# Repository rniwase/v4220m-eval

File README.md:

# v4220m-eval
V4220M Audio Codec IC Evaluation Board

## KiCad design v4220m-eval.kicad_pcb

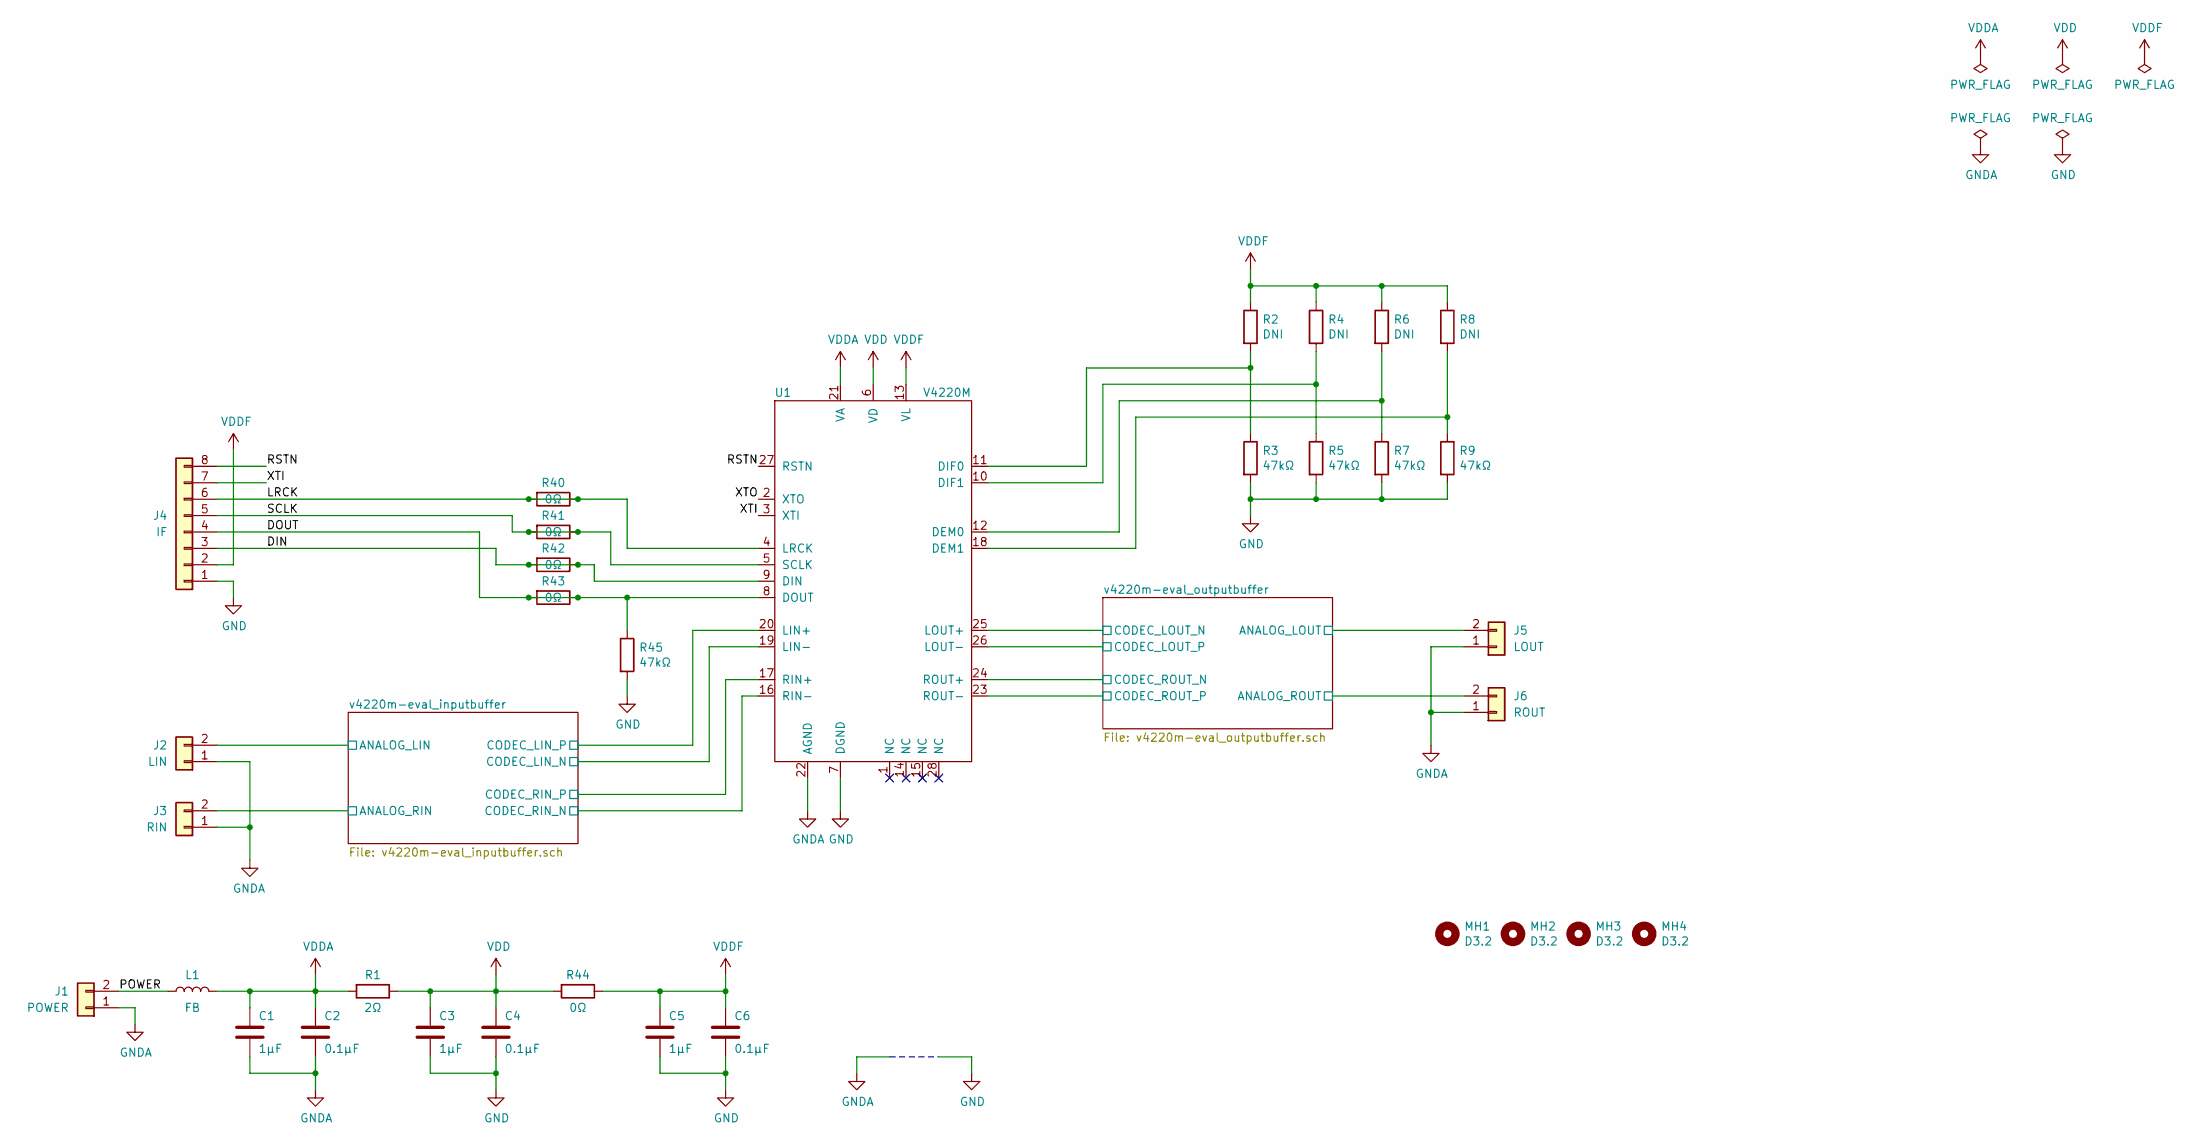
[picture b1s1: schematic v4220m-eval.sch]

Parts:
C1, C3, C5: 1μF; C_0603_1608Metric_Pad1.05x0.95mm_HandSolder
C2, C4, C6: 0.1μF; C_0603_1608Metric_Pad1.05x0.95mm_HandSolder
J1: POWER; PinHeader_1x02_P2.54mm_Vertical
J2: LIN; PinHeader_1x02_P2.54mm_Vertical
J3: RIN; PinHeader_1x02_P2.54mm_Vertical
J4: IF; PinHeader_1x08_P2.54mm_Vertical
J5: LOUT; PinHeader_1x02_P2.54mm_Vertical
J6: ROUT; PinHeader_1x02_P2.54mm_Vertical
L1: FB; L_0603_1608Metric_Pad1.05x0.95mm_HandSolder
MH1, MH2, MH3, MH4: D3.2; MountingHole_3.2mm_M3
R1: 2Ω; R_0603_1608Metric_Pad1.05x0.95mm_HandSolder
R2, R4, R6, R8: DNI; R_0603_1608Metric_Pad1.05x0.95mm_HandSolder
R3, R5, R7, R9, R45: 47kΩ; R_0603_1608Metric_Pad1.05x0.95mm_HandSolder
R40, R41, R42, R43, R44: 0Ω; R_0603_1608Metric_Pad1.05x0.95mm_HandSolder
U1: V4220M; SSOP-28_5.3x10.2mm_P0.65mm

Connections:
/DIN: J4.3, R42.1, R42.2, U1.9 (DIN)
/DOUT: J4.4, R43.1, R43.2, R45.1, U1.8 (DOUT)
/LRCK: J4.6, R40.1, R40.2, U1.4 (LRCK)
/POWER: J1.2, L1.1
/RSTN: J4.8, U1.27 (RSTN)
/SCLK: J4.5, R41.1, R41.2, U1.5 (SCLK)
/XTI: J4.7, U1.3 (XTI)
/v4220m-eval_inputbuffer/ANALOG_LIN: J2.2; also elsewhere on the board
/v4220m-eval_inputbuffer/ANALOG_RIN: J3.2; also elsewhere on the board
/v4220m-eval_inputbuffer/CODEC_LIN_N: U1.19 (LIN-); also elsewhere on the board
/v4220m-eval_inputbuffer/CODEC_LIN_P: U1.20 (LIN+); also elsewhere on the board
/v4220m-eval_inputbuffer/CODEC_RIN_N: U1.16 (RIN-); also elsewhere on the board
/v4220m-eval_inputbuffer/CODEC_RIN_P: U1.17 (RIN+); also elsewhere on the board
/v4220m-eval_outputbuffer/ANALOG_LOUT: J5.2; also elsewhere on the board
/v4220m-eval_outputbuffer/ANALOG_ROUT: J6.2; also elsewhere on the board
/v4220m-eval_outputbuffer/CODEC_LOUT_N: U1.25 (LOUT+); also elsewhere on the board
/v4220m-eval_outputbuffer/CODEC_LOUT_P: U1.26 (LOUT-); also elsewhere on the board
/v4220m-eval_outputbuffer/CODEC_ROUT_N: U1.24 (ROUT+); also elsewhere on the board
/v4220m-eval_outputbuffer/CODEC_ROUT_P: U1.23 (ROUT-); also elsewhere on the board
GND: C3.2, C4.2, C5.2, C6.2, J4.1, R3.2, R5.2, R7.2, R9.2, R45.2, U1.7 (DGND)
GNDA: C1.2, C2.2, J1.1, J2.1, J3.1, J5.1, J6.1, U1.22 (AGND); also elsewhere on the board
unnamed: R2.2, R3.1, U1.11 (DIF0)
unnamed: R4.2, R5.1, U1.10 (DIF1)
unnamed: R6.2, R7.1, U1.12 (DEM0)
unnamed: R8.2, R9.1, U1.18 (DEM1)
VDD: C3.1, C4.1, R1.1, R44.2, U1.6 (VD)
VDDA: C1.1, C2.1, L1.2, R1.2, U1.21 (VA); also elsewhere on the board
VDDF: C5.1, C6.1, J4.2, R2.1, R4.1, R6.1, R8.1, R44.1, U1.13 (VL)

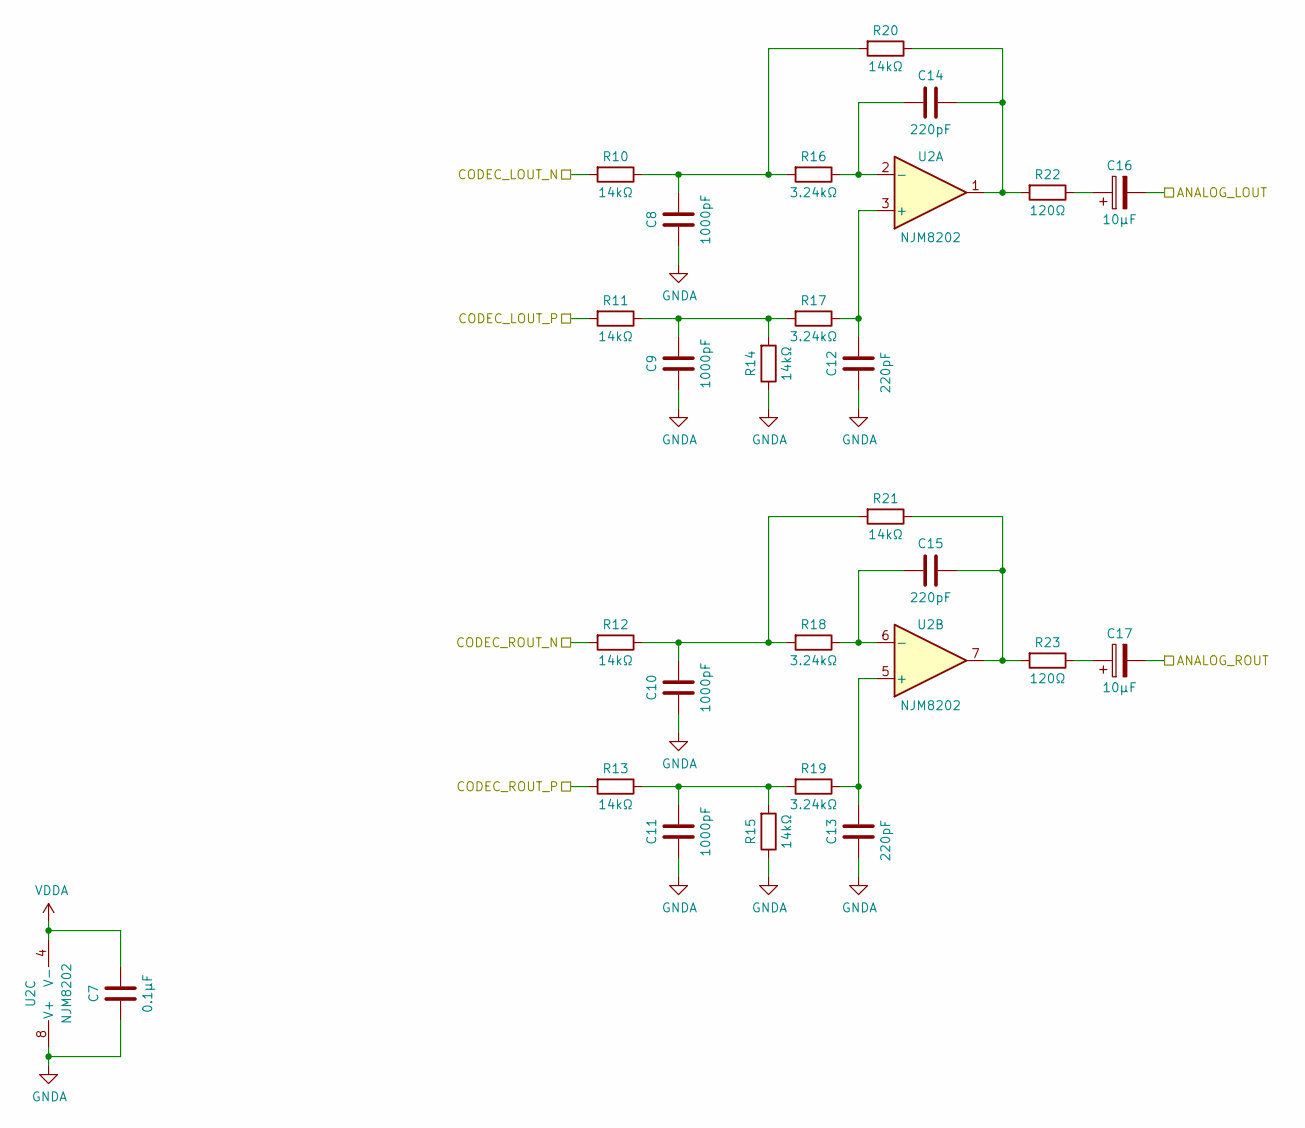
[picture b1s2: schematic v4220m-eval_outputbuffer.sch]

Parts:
C7: 0.1μF; C_0603_1608Metric_Pad1.05x0.95mm_HandSolder
C8, C9, C10, C11: 1000pF; C_0603_1608Metric_Pad1.05x0.95mm_HandSolder
C12, C13, C14, C15: 220pF; C_0603_1608Metric_Pad1.05x0.95mm_HandSolder
C16, C17: 10μF; CP_Elec_4x5.3
R10, R11, R12, R13, R14, R15, R20, R21: 14kΩ; R_0603_1608Metric_Pad1.05x0.95mm_HandSolder
R16, R17, R18, R19: 3.24kΩ; R_0603_1608Metric_Pad1.05x0.95mm_HandSolder
R22, R23: 120Ω; R_0603_1608Metric_Pad1.05x0.95mm_HandSolder
U2: NJM8202; MSOP-8_3x3mm_P0.65mm

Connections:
/v4220m-eval_outputbuffer/ANALOG_LOUT: C16.2; also elsewhere on the board
/v4220m-eval_outputbuffer/ANALOG_ROUT: C17.2; also elsewhere on the board
/v4220m-eval_outputbuffer/CODEC_LOUT_N: R10.2; also elsewhere on the board
/v4220m-eval_outputbuffer/CODEC_LOUT_P: R11.2; also elsewhere on the board
/v4220m-eval_outputbuffer/CODEC_ROUT_N: R12.2; also elsewhere on the board
/v4220m-eval_outputbuffer/CODEC_ROUT_P: R13.2; also elsewhere on the board
GNDA: C7.1, C8.1, C9.1, C10.1, C11.1, C12.1, C13.1, R14.1, R15.1, U2.8 (V+); also elsewhere on the board
unnamed: C8.2, R10.1, R16.2, R20.2
unnamed: C9.2, R11.1, R14.2, R17.2
unnamed: C10.2, R12.1, R18.2, R21.2
unnamed: C11.2, R13.1, R15.2, R19.2
unnamed: C12.2, R17.1, U2.3 (+)
unnamed: C13.2, R19.1, U2.5 (+)
unnamed: C14.1, R20.1, R22.2, U2.1
unnamed: C14.2, R16.1, U2.2 (-)
unnamed: C15.1, R21.1, R23.2, U2.7
unnamed: C15.2, R18.1, U2.6 (-)
unnamed: C16.1, R22.1
unnamed: C17.1, R23.1
VDDA: C7.2, U2.4 (V-); also elsewhere on the board

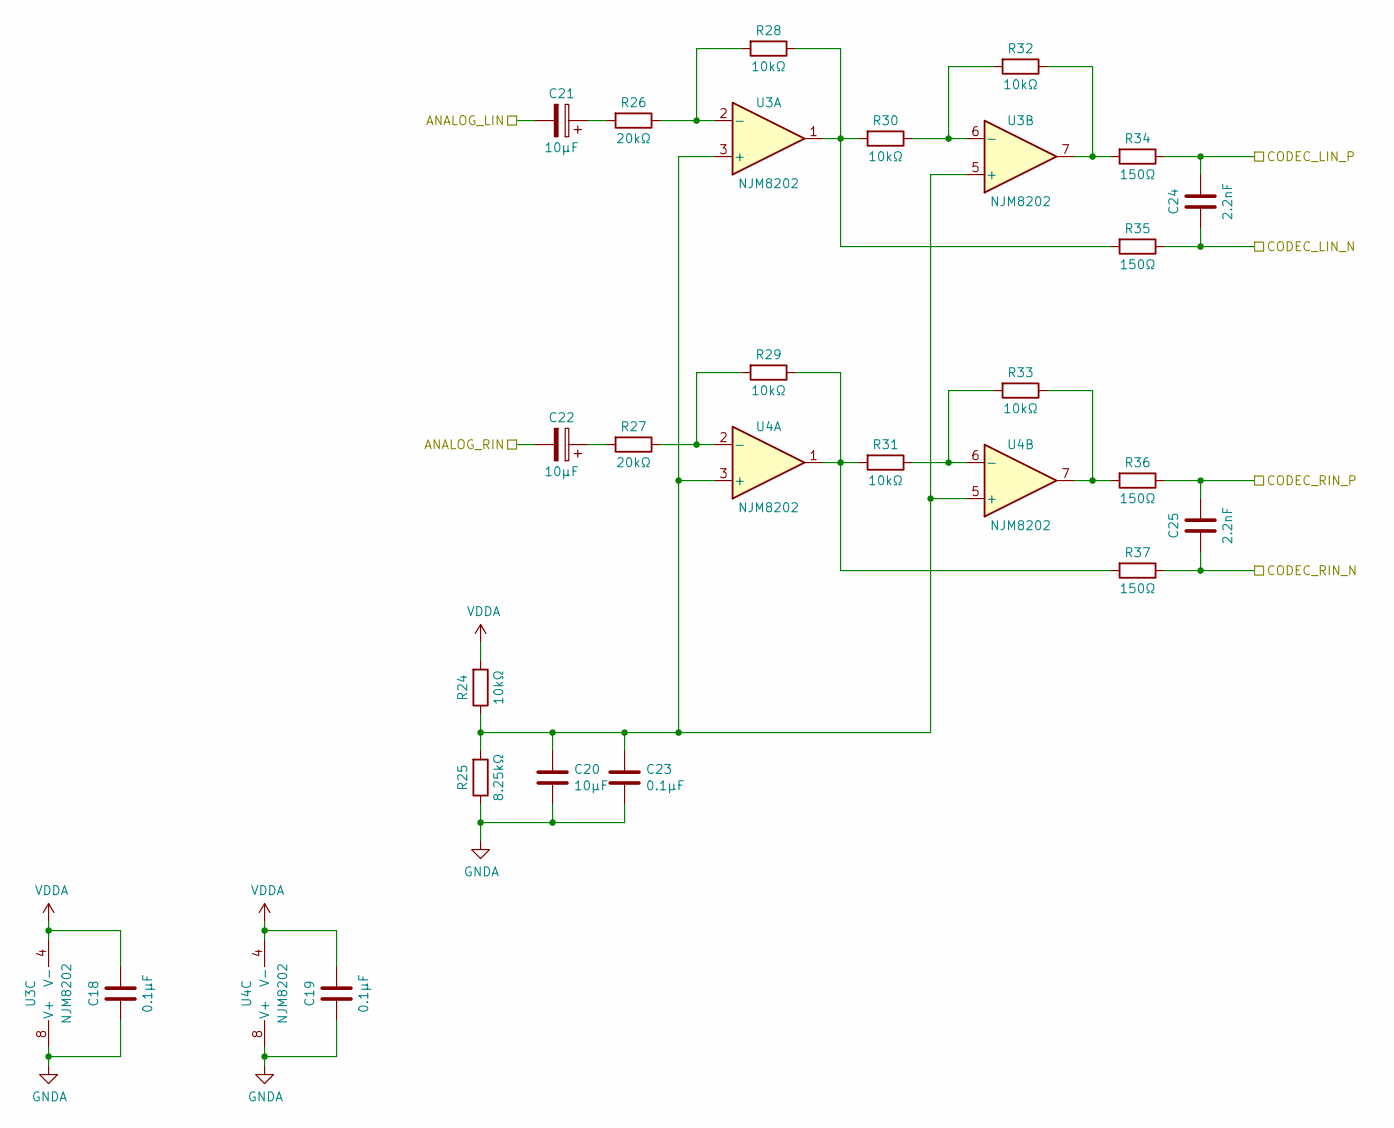
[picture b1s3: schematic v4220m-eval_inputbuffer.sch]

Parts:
C18, C19, C23: 0.1μF; C_0603_1608Metric_Pad1.05x0.95mm_HandSolder
C20: 10μF; C_0603_1608Metric_Pad1.05x0.95mm_HandSolder
C21, C22: 10μF; CP_Elec_4x5.3
C24, C25: 2.2nF; C_0603_1608Metric_Pad1.05x0.95mm_HandSolder
R24, R28, R29, R30, R31, R32, R33: 10kΩ; R_0603_1608Metric_Pad1.05x0.95mm_HandSolder
R25: 8.25kΩ; R_0603_1608Metric_Pad1.05x0.95mm_HandSolder
R26, R27: 20kΩ; R_0603_1608Metric_Pad1.05x0.95mm_HandSolder
R34, R35, R36, R37: 150Ω; R_0603_1608Metric_Pad1.05x0.95mm_HandSolder
U3, U4: NJM8202; MSOP-8_3x3mm_P0.65mm

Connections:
/v4220m-eval_inputbuffer/ANALOG_LIN: C21.2; also elsewhere on the board
/v4220m-eval_inputbuffer/ANALOG_RIN: C22.2; also elsewhere on the board
/v4220m-eval_inputbuffer/CODEC_LIN_N: C24.1, R35.1; also elsewhere on the board
/v4220m-eval_inputbuffer/CODEC_LIN_P: C24.2, R34.1; also elsewhere on the board
/v4220m-eval_inputbuffer/CODEC_RIN_N: C25.1, R37.1; also elsewhere on the board
/v4220m-eval_inputbuffer/CODEC_RIN_P: C25.2, R36.1; also elsewhere on the board
GNDA: C18.1, C19.1, C20.2, C23.2, R25.1, U3.8 (V+), U4.8 (V+); also elsewhere on the board
unnamed: C20.1, C23.1, R24.1, R25.2, U3.3 (+), U3.5 (+), U4.3 (+), U4.5 (+)
unnamed: C21.1, R26.2
unnamed: C22.1, R27.2
unnamed: R26.1, R28.2, U3.2 (-)
unnamed: R27.1, R29.2, U4.2 (-)
unnamed: R28.1, R30.2, R35.2, U3.1
unnamed: R29.1, R31.2, R37.2, U4.1
unnamed: R30.1, R32.2, U3.6 (-)
unnamed: R31.1, R33.2, U4.6 (-)
unnamed: R32.1, R34.2, U3.7
unnamed: R33.1, R36.2, U4.7
VDDA: C18.2, C19.2, R24.2, U3.4 (V-), U4.4 (V-); also elsewhere on the board

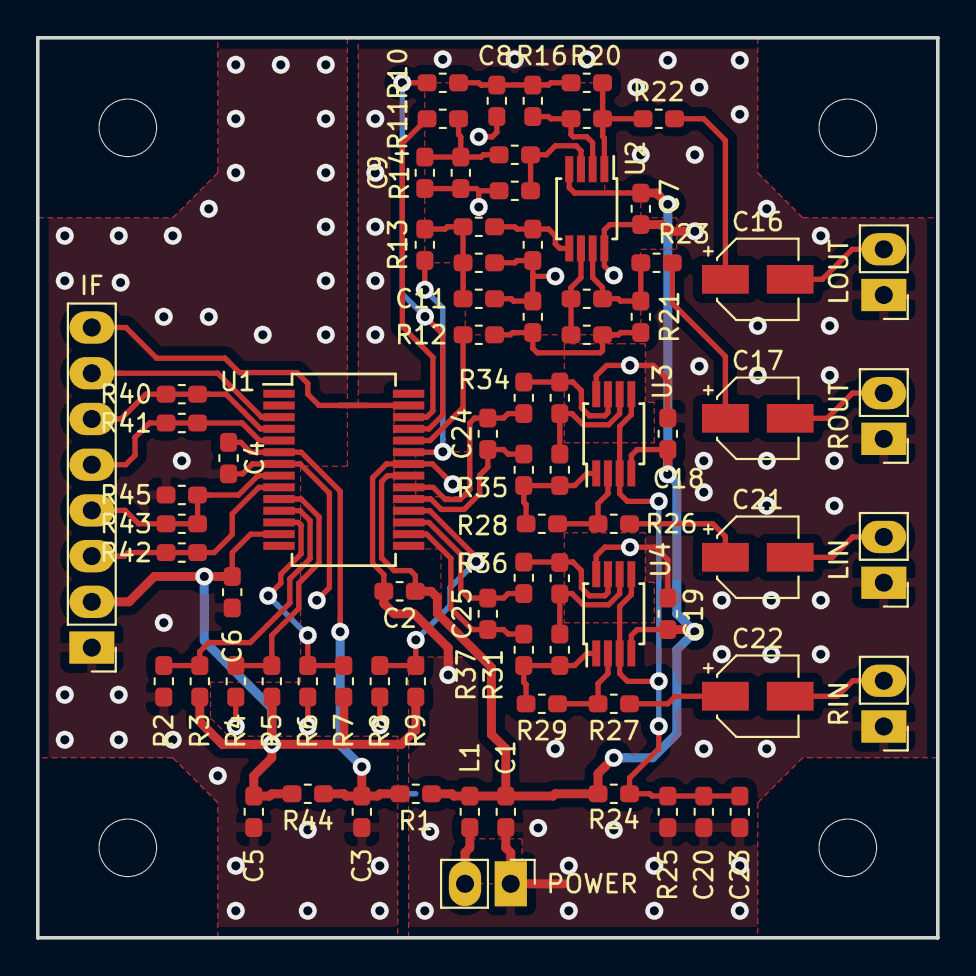
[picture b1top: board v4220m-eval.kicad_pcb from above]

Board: 2 copper layers, 50.0 x 50.0 mm, 83 parts (0 on the bottom side), 51 nets.

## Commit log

2021-03-18 fix i2s din/dout net
